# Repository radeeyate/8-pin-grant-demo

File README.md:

# 8 Pin Grant Demo Board

This repository contains a demo board for [8 Pin Grant](https://8-pin-grant.hackclub.com/)

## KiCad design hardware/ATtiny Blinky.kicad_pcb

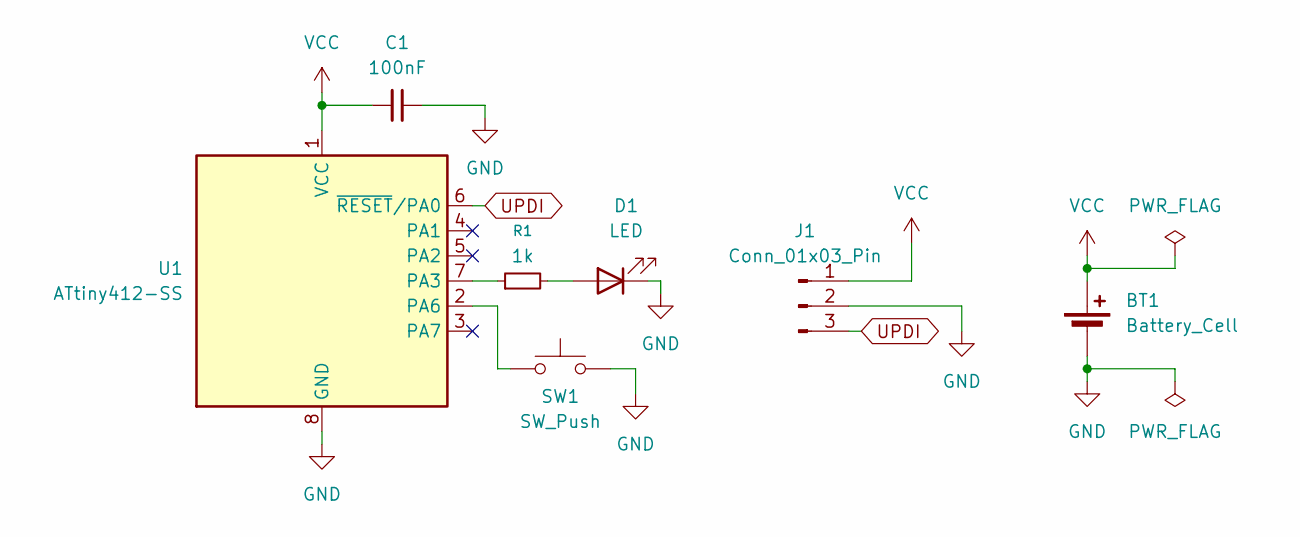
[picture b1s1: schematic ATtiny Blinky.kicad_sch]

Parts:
BT1: Battery_Cell; BatteryHolder_Keystone_3002_1x2032
C1: 100nF; C_0603_1608Metric
D1: LED; LED_0805_2012Metric
J1: Conn_01x03_Pin; PinHeader_1x03_P2.54mm_Vertical
R1: 1k; R_0603_1608Metric
SW1: SW_Push; SW_Push_SPST_NO_Alps_SKRK
U1: ATtiny412-SS; SOIC-8_3.9x4.9mm_P1.27mm

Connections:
GND: BT1.2 (-), C1.2, D1.1 (K), J1.2, SW1.2, U1.8 (GND)
unnamed: D1.2 (A), R1.2
unnamed: R1.1, U1.7 (PA3)
unnamed: SW1.1, U1.2 (PA6)
UPDI: J1.3, U1.6 (~RESET/PA0)
VCC: BT1.1 (+), C1.1, J1.1, U1.1 (VCC)

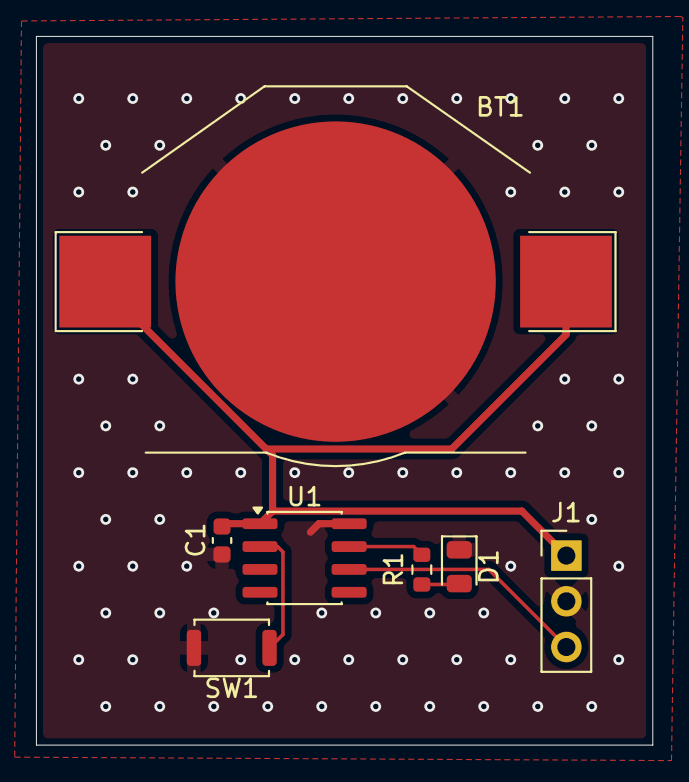
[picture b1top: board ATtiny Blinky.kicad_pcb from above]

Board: 2 copper layers, 34.2 x 39.4 mm, 7 parts (0 on the bottom side), 6 nets.
